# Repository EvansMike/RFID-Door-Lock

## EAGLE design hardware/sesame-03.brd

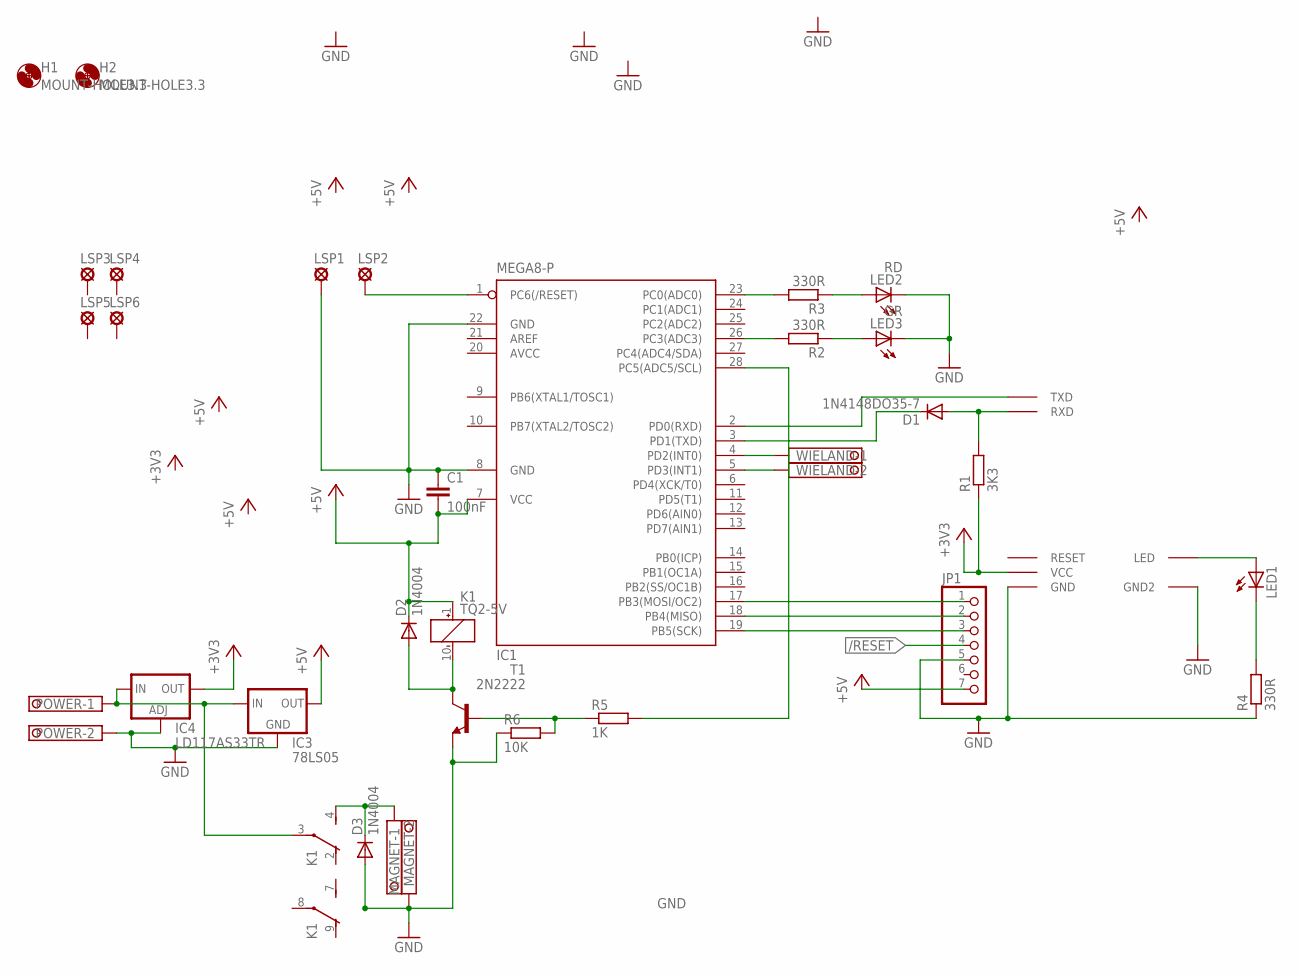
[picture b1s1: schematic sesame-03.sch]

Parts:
C1: 100nF; C025-030X050
D1: 1N4148DO35-7; DO35-7
D2, D3: 1N4004; DO41-10
H1, H2: MOUNT-HOLE3.3; 3,3
IC1: MEGA8-P; DIL28-3
IC3: 78LS05; 78LXX
IC4: LD117AS33TR; SOT223
JP1: PINHD-1X7; 1X07
K1: TQ2-5V; TQ2
LED1: LED3MM
LED2: RD; LED5MM
LED3: GR; LED5MM
LSP1, LSP2, LSP3, LSP4, LSP5, LSP6: LSP13
MAGNET: 1751248
POWER: 1751248
R1: 3K3; 0204/7
R2, R3, R4: 330R; 0204/7
R5: 1K; 0204/7
R6: 10K; 0204/7
T1: 2N2222; TO18
U$1: HR5; BLUETOOTH_MODULE
WIELAND: 1751248

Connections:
12V: IC3.IN, IC4.3 (IN), K1.3, POWER.1
+3V3: IC4.4 (OUT), R1.1, U$1.P$12 (VCC)
+5V: C1.2, D2.C, IC1.7 (VCC), IC3.OUT, JP1.7, K1.1 (+)
/RESET: IC1.1 (PC6(/RESET)), JP1.4, LSP2.MP
AVCC: IC1.20 (AVCC)
GND: C1.1, D3.A, IC1.8 (GND), IC1.22 (GND), IC3.GND, IC4.1 (ADJ), JP1.5, LED2.K (C), LED3.K (C), LSP1.MP, MAGNET.2, POWER.2, R4.1, R6.1, T1.1 (E), U$1.P$13 (GND), U$1.P$22 (GND2)
unnamed: IC1.2 (PD0(RXD)), U$1.P$1 (TXD)
unnamed: IC1.28 (PC5(ADC5/SCL)), R5.2
unnamed: IC1.26 (PC3(ADC3)), R2.2
unnamed: LED3.A, R2.1
unnamed: D1.C, IC1.3 (PD1(TXD))
unnamed: IC1.23 (PC0(ADC0)), R3.2
unnamed: IC1.19 (PB5(SCK)), JP1.3
unnamed: IC1.18 (PB4(MISO)), JP1.2
unnamed: IC1.17 (PB3(MOSI/OC2)), JP1.1
unnamed: D3.C, K1.4 (S), MAGNET.1
unnamed: LED1.A, U$1.P$24 (LED)
unnamed: D1.A, R1.2, U$1.P$2 (RXD)
unnamed: R5.1, R6.2, T1.2 (B)
unnamed: IC1.4 (PD2(INT0)), WIELAND.1
unnamed: IC1.5 (PD3(INT1)), WIELAND.2
unnamed: LED2.A, R3.1
unnamed: LED1.K (C), R4.2
unnamed: D2.A, K1.10 (-), T1.3 (C)

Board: 2 copper layers, 31 parts (2 on the bottom side), 23 nets, no tracks yet.

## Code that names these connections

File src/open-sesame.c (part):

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 *
 *
 * OUTPUTS:
 * PC3 - LED GREEN
 * PC0 - LED RED
 * PC5 - RELAY_ DOOR
 *
 * INPUTS:
 * RX - Bluetooth module direct
 * TX - Bluetooth via Diode and pullup to 3.3V
 *
 * PD2 - WIEGAND-0 RFID Reader
 * PD3 - WIEGAND-1 RFID Reader
 *
 *
 *
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
#define IOPORT PORTC
#define DDR_IOPORT DDRC
#define LED_G PC3
#define LED_R PC0
#define RELAY PC5
#define SWITCH PC4
#define READER_LED PD5
#define READER_BEEP PD6

// Next two are defined in wiegand.c, here for reference.
#define W0 PD2
#define W1 PD3

// Static function definitions.
static void list_recent(void);
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
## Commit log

2018-06-01 Removed old repo completeley.
    The direction I was taking was overkill for this project. I could probably
    use an ATtiny of some sort for this as the required pin count does
    not warrant a ATmega.
2018-06-01 Clean up code.
2018-06-01 Add kikad files,
2018-06-02 removed generated files from git.
2018-06-02 Generate BT PIN from last 4 digits of master card.
2018-06-02 modified: ../README.asc
2018-06-02 Typo.
2018-06-02 Add more to README.
2018-06-02 Bug#177
    - Connect reader LED and use it indicate success
    - Connect reader beeper and use it to indicate failure.
2018-06-02 Don't clobber current setting on PORTD.
2018-06-02 I really should test BEFORE I push.
2018-06-02 Remove bogus files,
2018-06-02 new file: doc/sesame_manual.asc
2018-06-03 Spellin'
2018-06-03 Make most functions static. Some line spacing.
2018-06-03 modified: ../README.asc modified: open-sesame.c
2018-06-03 Add some optimiseations in the Makefile, Code shrunk by 1748 bytes
2018-06-04 Added CRLF to messages.
2018-06-05 Ooops. I wasn't setting the BT PIN on first card.
2018-06-05 Bug#180 Add factory reset switch.
2018-06-05 Bug#180 Move PORTD init stuff.
2018-06-05 Bug#180 Do the factory reset stuff.
2019-04-27 Put LED colours on schematic.
2019-04-27 Add missing +5V relay supply.
2019-04-27 Add missing power regulator and connector.
2019-04-27 Remove beep and LED stuff. Did't really work.
2019-05-02 Increase text buffer length by 1
    Some de-crufting.

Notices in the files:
src/open-sesame.c:
Copyright 2014 Mike Evans <mikee@saxicola.co.uk>
This program is free software; you can redistribute it and/or modify
it under the terms of the GNU General Public License as published by
the Free Software Foundation; either version 2 of the License, or
(at your option) any later version.
